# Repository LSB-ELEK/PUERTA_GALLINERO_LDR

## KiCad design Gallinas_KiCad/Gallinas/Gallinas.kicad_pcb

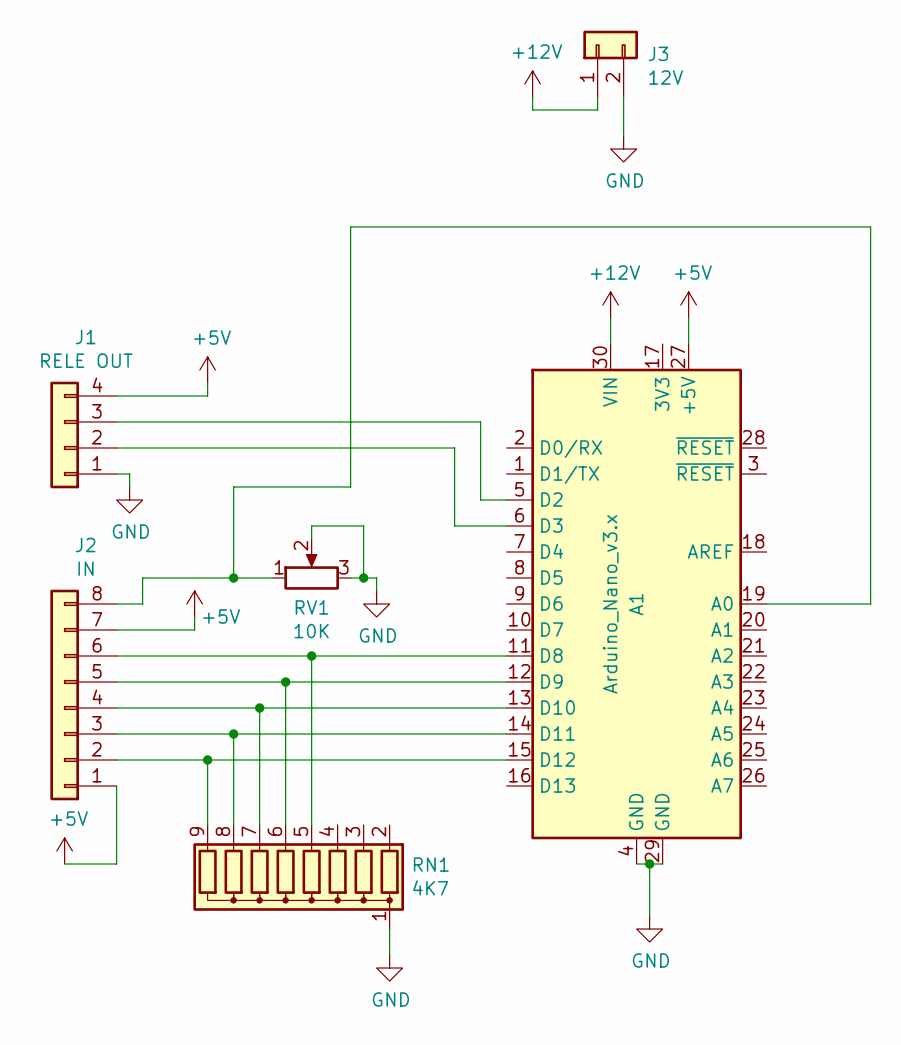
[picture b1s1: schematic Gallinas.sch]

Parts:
A1: Arduino_Nano_v3.x; Arduino_Nano
J1: RELE OUT; TerminalBlock_bornier-4_P5.08mm
J2: IN; TerminalBlock_RND_205-00238_1x08_P5.08mm_Horizontal
J3: 12V; TerminalBlock_bornier-2_P5.08mm
RN1: 4K7; R_Array_SIP9
RV1: 10K; Potentiometer_ACP_CA6-H2,5_Horizontal

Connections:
+5V: A1.27 (+5V), J1.4, J2.1, J2.7
+12V: A1.30 (VIN), J3.1
GND: A1.4 (GND), A1.29 (GND), J1.1, J3.2, RN1.1 (common), RV1.2, RV1.3
unnamed: A1.5 (D2), J1.3
unnamed: A1.6 (D3), J1.2
unnamed: A1.11 (D8), J2.6, RN1.5 (R4)
unnamed: A1.12 (D9), J2.5, RN1.6 (R5)
unnamed: A1.13 (D10), J2.4, RN1.7 (R6)
unnamed: A1.14 (D11), J2.3, RN1.8 (R7)
unnamed: A1.15 (D12), J2.2, RN1.9 (R8)
unnamed: A1.19 (A0), J2.8, RV1.1

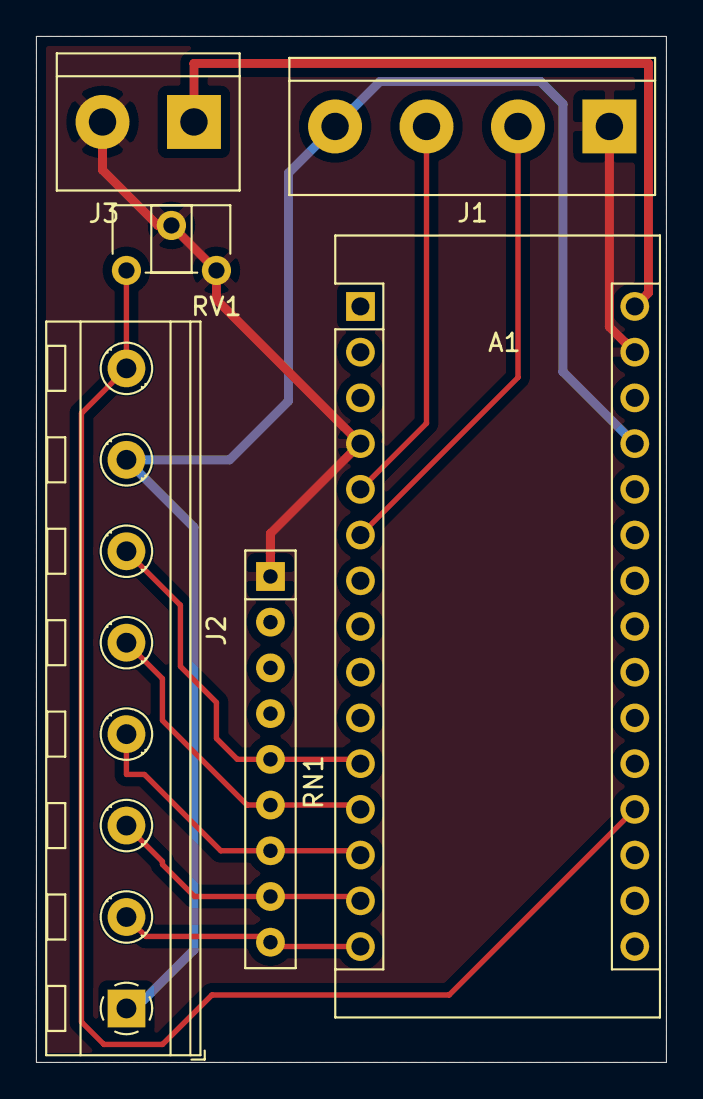
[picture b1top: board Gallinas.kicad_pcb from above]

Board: 2 copper layers, 35.0 x 57.0 mm, 6 parts (0 on the bottom side), 11 nets.

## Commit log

2021-06-10 Proreus
2021-06-10 Upload
2021-06-10 KiCad
2021-06-16 ARROWs
